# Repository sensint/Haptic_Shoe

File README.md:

<div id="top"></div>

<!-- PROJECT SHIELDS -->
<!--
*** I'm using markdown "reference style" links for readability.
*** Reference links are enclosed in brackets [ ] instead of parentheses ( ).
*** See the bottom of this document for the declaration of the reference variables
*** for contributors-url, forks-url, etc. This is an optional, concise syntax you may use.
*** https://www.markdownguide.org/basic-syntax/#reference-style-links
-->
[![Contributors][contributors-shield]][contributors-url]
[![Forks][forks-shield]][forks-url]
[![Stargazers][stars-shield]][stars-url]
[![Issues][issues-shield]][issues-url]
[![MIT License][license-shield]][license-url]

<!-- PROJECT LOGO -->
<br />
<div align="center">

<h3 align="center">Haptic Shoe</h3>

  <p align="center">
    An Open Source Experimental Haptic Shoe for Augmented Tactile Reality
    <br />
    <br />
    <a href="https://github.com/sensint/Haptic_Shoe/issues">Report Bug</a>
    ·
    <a href="https://github.com/sensint/Haptic_Shoe/issues">Request Feature</a>
  </p>
</div>

## About The Project

![Banner images][banner-image]

<!--Add a summary of the project.-->

<p align="right">(<a href="#top">back to top</a>)</p>

### Built With

* [Teensy](https://www.pjrc.com/teensy/) and [Teensy Audio Library](https://www.pjrc.com/teensy/td_libs_Audio.html)
* [PlatformIO](https://platformio.org/)
* [Fusion 360](https://www.autodesk.com/products/fusion-360)
* [KiCad EDA](https://www.kicad.org/)

<p align="right">(<a href="#top">back to top</a>)</p>

## Getting Started

Download the code from the GitHub website or clone the repository using your favorite git-client software or with the following command:

   ```sh
   git clone https://github.com/sensint/Haptic_Shoe.git
   ```

### Firmware

<p align="right">(<a href="#top">back to top</a>)</p>

### Hardware

<p align="right">(<a href="#top">back to top</a>)</p>

## Usage

<!--Use this space to show useful examples of how a project can be used. Additional screenshots, code examples and demos work well in this space. You may also link to more resources.-->

<p align="right">(<a href="#top">back to top</a>)</p>

## Roadmap

See the [open issues](https://github.com/sensint/Haptic_Shoe/issues) for a full list of proposed features (and known issues).

### Firmware

- [ ] ...

### Hardware

- [ ] ...

<p align="right">(<a href="#top">back to top</a>)</p>

## Contributing

Contributions are what make the open source community such an amazing place to learn, inspire, and create. Any contributions you make are **greatly appreciated**.

If you have a suggestion that would make this better, please fork the repo and create a pull request. You can also simply open an issue with the tag "enhancement".
Don't forget to give the project a star! Thanks again!

1. Fork the Project
2. Create your Feature Branch (`git checkout -b feature/AmazingFeature`)
3. Commit your Changes (`git commit -m 'Add some AmazingFeature'`)
4. Push to the Branch (`git push origin feature/AmazingFeature`)
5. Open a Pull Request

<p align="right">(<a href="#top">back to top</a>)</p>

## License

Distributed under the MIT License. See `LICENSE.txt` for more information.

<p align="right">(<a href="#top">back to top</a>)</p>

## Contact

Sensorimotor Interaction Group - [website](https://sensint.mpi-inf.mpg.de/) - [@sensintgroup](https://twitter.com/sensintgroup)

Project Link: [https://github.com/sensint/Haptic_Shoe](https://github.com/sensint/Haptic_Shoe)

<p align="right">(<a href="#top">back to top</a>)</p>

## Acknowledgments

* Othneil Drew for [Best-README-Template](https://github.com/othneildrew/Best-README-Template)

<p align="right">(<a href="#top">back to top</a>)</p>

<!-- MARKDOWN LINKS & IMAGES -->
<!-- https://www.markdownguide.org/basic-syntax/#reference-style-links -->
[contributors-shield]: https://img.shields.io/github/contributors/sensint/Haptic_Shoe.svg?style=for-the-badge
[contributors-url]: https://github.com/sensint/Haptic_Shoe/graphs/contributors
[forks-shield]: https://img.shields.io/github/forks/sensint/Haptic_Shoe.svg?style=for-the-badge
[forks-url]: https://github.com/sensint/Haptic_Shoe/network/members
[stars-shield]: https://img.shields.io/github/stars/sensint/Haptic_Shoe.svg?style=for-the-badge
[stars-url]: https://github.com/sensint/Haptic_Shoe/stargazers
[issues-shield]: https://img.shields.io/github/issues/sensint/Haptic_Shoe.svg?style=for-the-badge
[issues-url]: https://github.com/sensint/Haptic_Shoe/issues
[license-shield]: https://img.shields.io/github/license/sensint/Haptic_Shoe.svg?style=for-the-badge
[license-url]: https://github.com/sensint/Haptic_Shoe/blob/master/LICENSE
[banner-image]: assets/img/banner.png

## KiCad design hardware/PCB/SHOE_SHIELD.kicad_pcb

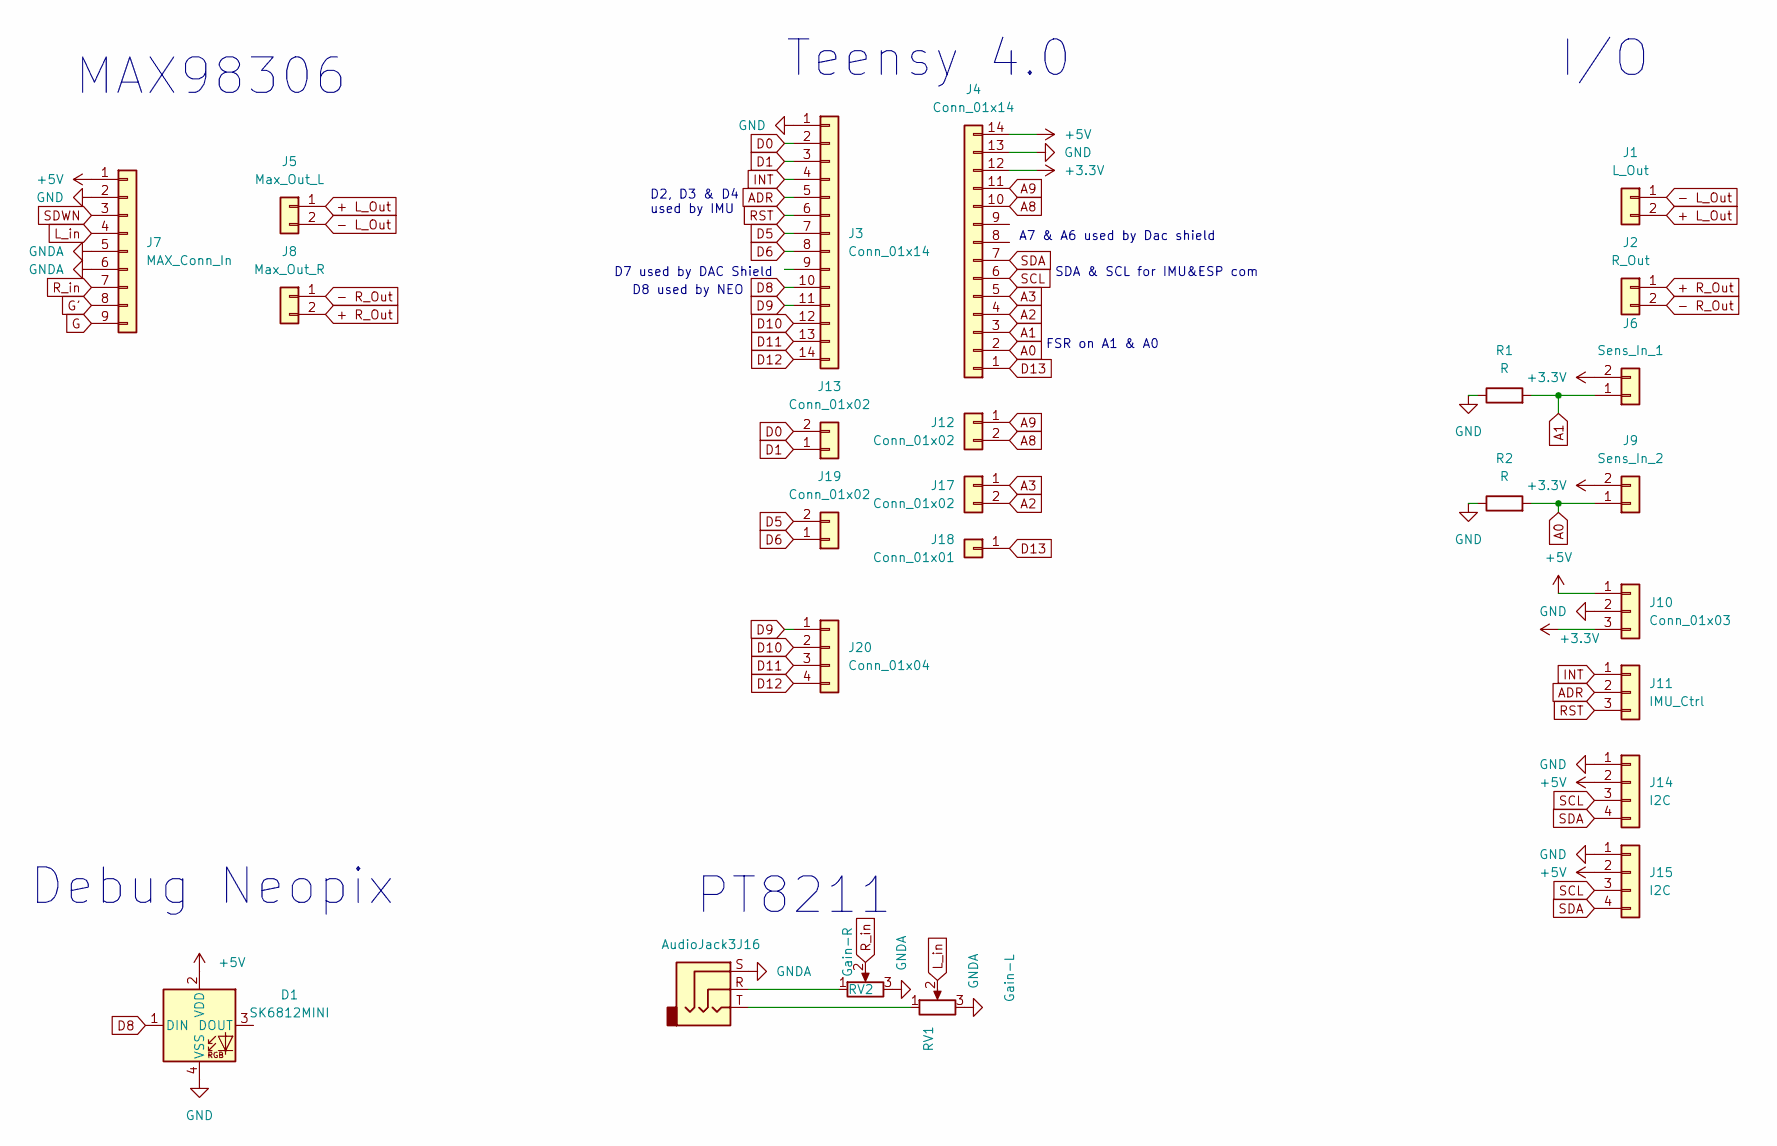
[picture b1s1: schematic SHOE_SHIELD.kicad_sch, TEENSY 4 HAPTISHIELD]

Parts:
D1: SK6812MINI; LED_SK6812MINI_PLCC4_3.5x3.5mm_P1.75mm
J1: L_Out; PinHeader_1x02_P2.54mm_Vertical
J2: R_Out; PinHeader_1x02_P2.54mm_Vertical
J3, J4: Conn_01x14; PinSocket_1x14_P2.54mm_Vertical
J5: Max_Out_L; TerminalBlock_MetzConnect_Type059_RT06302HBWC_1x02_P3.50mm_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
J6: Sens_In_1; PinHeader_1x02_P2.54mm_Vertical
J7: MAX_Conn_In; PinSocket_1x09_P2.54mm_Vertical
J8: Max_Out_R; TerminalBlock_MetzConnect_Type059_RT06302HBWC_1x02_P3.50mm_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
J9: Sens_In_2; PinHeader_1x02_P2.54mm_Vertical
J10: Conn_01x03; PinHeader_1x03_P2.54mm_Vertical
J11: IMU_Ctrl; PinHeader_1x03_P2.54mm_Vertical
J12, J13, J17, J19: Conn_01x02; PinHeader_1x02_P2.54mm_Vertical
J14, J15: I2C; PinHeader_1x04_P2.54mm_Vertical
J16: AudioJack3; Jack_3.5mm_CUI_SJ1-3525N_Horizontal
J18: Conn_01x01; PinHeader_1x01_P2.54mm_Vertical
J20: Conn_01x04; PinHeader_1x04_P2.54mm_Vertical
R1, R2: R; R_Axial_DIN0204_L3.6mm_D1.6mm_P2.54mm_Vertical
RV1: Gain-L; Potentiometer_Runtron_RM-065_Vertical
RV2: Gain-R; Potentiometer_Runtron_RM-065_Vertical

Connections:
+3V3: J4.12, J6.2, J9.2, J10.3
+5V: D1.2 (VDD), J4.14, J7.1, J10.1, J14.2, J15.2
+ L_Out: J1.2, J5.1
+ R_Out: J2.1, J8.2
- L_Out: J1.1, J5.2
- R_Out: J2.2, J8.1
A0: J4.2, J9.1, R2.2
A1: J4.3, J6.1, R1.2
A2: J4.4, J17.2
A3: J4.5, J17.1
A8: J4.10, J12.2
A9: J4.11, J12.1
ADR: J3.5, J11.2
D0: J3.2, J13.2
D1: J3.3, J13.1
D5: J3.7, J19.2
D6: J3.8, J19.1
D8: D1.1 (DIN), J3.10
D9: J3.11, J20.1
D10: J3.12, J20.2
D11: J3.13, J20.3
D12: J3.14, J20.4
D13: J4.1, J18.1
G: J7.9
G': J7.8
GND: D1.4 (VSS), J3.1, J4.13, J7.2, J10.2, J14.1, J15.1, R1.1, R2.1
GNDA: J7.5, J7.6, J16.S, RV1.3, RV2.3
INT: J3.4, J11.1
L_in: J7.4, RV1.2
unnamed: J16.R, RV2.1
unnamed: J16.T, RV1.1
RST: J3.6, J11.3
R_in: J7.7, RV2.2
SCL: J4.6, J14.3, J15.3
SDA: J4.7, J14.4, J15.4
SDWN: J7.3

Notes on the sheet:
PT8211
D2, D3 & D4 used by IMU
SDA & SCL for IMU&ESP com
Teensy 4.0
FSR on A1 & A0
D7 used by DAC Shield
A7 & A6 used by Dac shield
D8 used by NEO
I/O
Debug Neopix
MAX98306

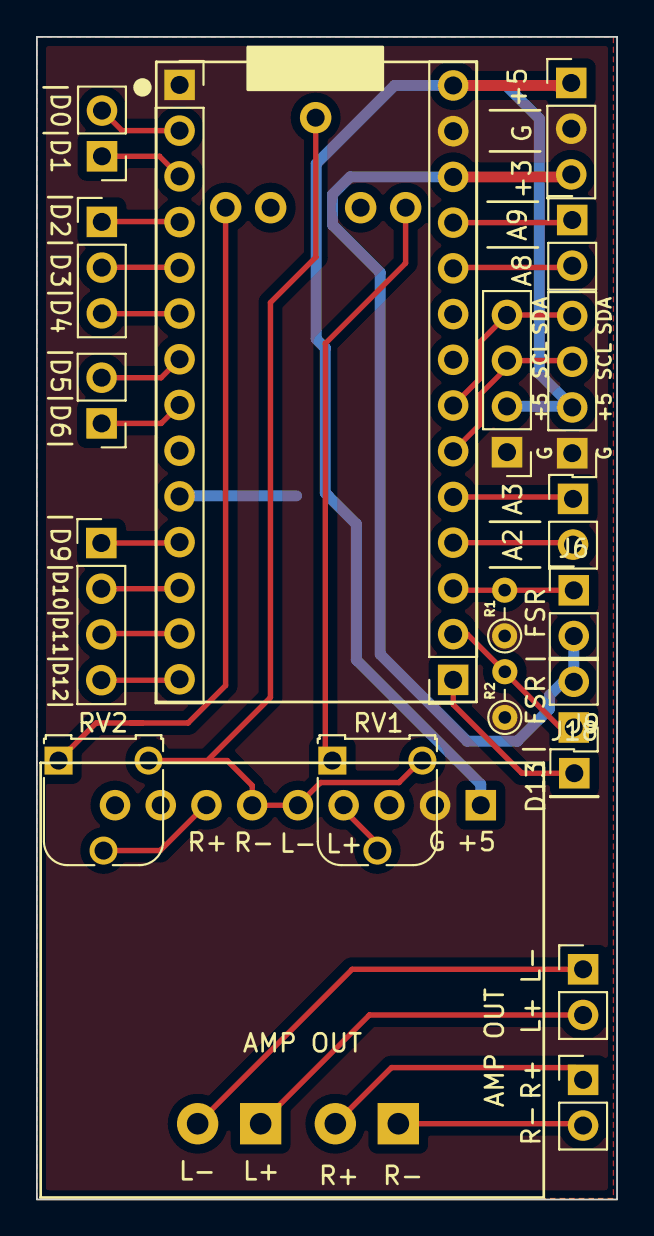
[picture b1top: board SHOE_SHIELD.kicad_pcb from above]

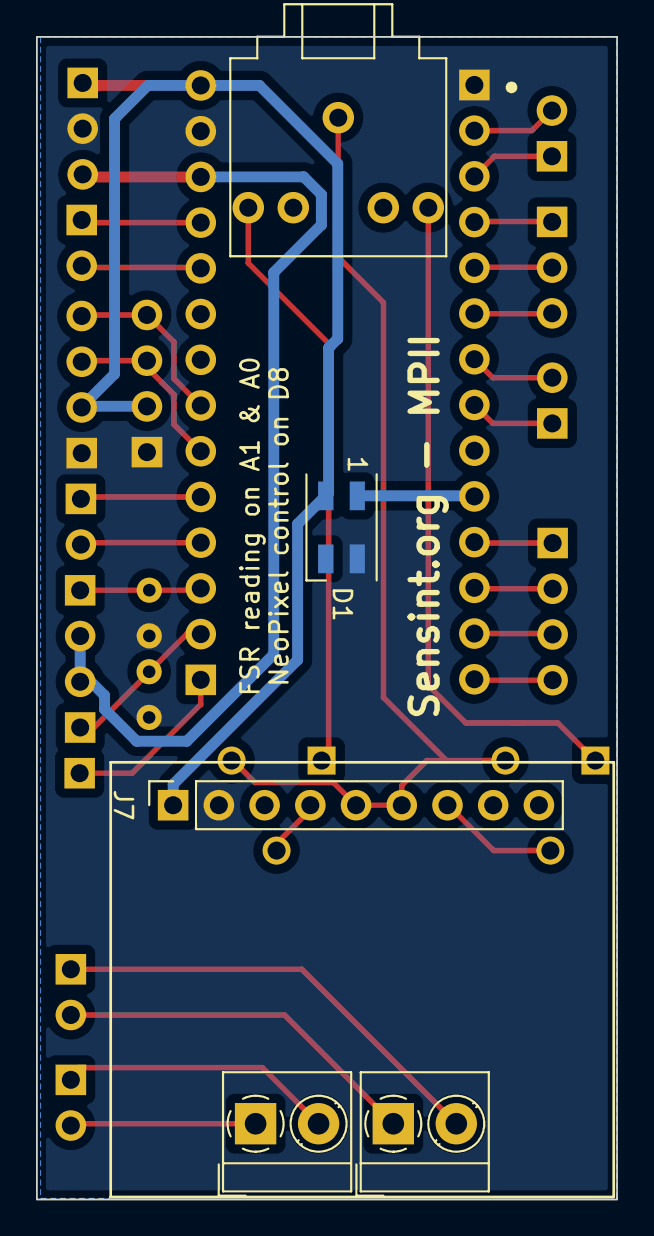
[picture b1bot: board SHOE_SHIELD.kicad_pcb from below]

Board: 2 copper layers, 32.2 x 64.6 mm, 25 parts (5 on the bottom side), 33 nets.

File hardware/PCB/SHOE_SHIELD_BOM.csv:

"Id";"Designator";"Package";"Quantity";"Designation";"Supplier and ref";
1;"R1,R2";"R_Axial_DIN0204_L3.6mm_D1.6mm_P2.54mm_Vertical";2;"R";;;
2;"J1";"PinHeader_1x02_P2.54mm_Vertical";1;"L_Out";;;
3;"J13,J12,J19,J17";"PinHeader_1x02_P2.54mm_Vertical";4;"Conn_01x02";;;
4;"J14,J15";"PinHeader_1x04_P2.54mm_Vertical";2;"I2C";;;
5;"J10";"PinHeader_1x03_P2.54mm_Vertical";1;"Conn_01x03";;;
6;"J6";"PinHeader_1x02_P2.54mm_Vertical";1;"Sens_In_1";;;
7;"J9";"PinHeader_1x02_P2.54mm_Vertical";1;"Sens_In_2";;;
8;"J11";"PinHeader_1x03_P2.54mm_Vertical";1;"IMU_Ctrl";;;
9;"RV1";"Potentiometer_Runtron_RM-065_Vertical";1;"Gain-L";;;
10;"J20";"PinHeader_1x04_P2.54mm_Vertical";1;"Conn_01x04";;;
11;"J2";"PinHeader_1x02_P2.54mm_Vertical";1;"R_Out";;;
12;"J4,J3";"PinSocket_1x14_P2.54mm_Vertical";2;"Conn_01x14";;;
13;"RV2";"Potentiometer_Runtron_RM-065_Vertical";1;"Gain-R";;;
14;"J18";"PinHeader_1x01_P2.54mm_Vertical";1;"Conn_01x01";;;
15;"D1";"LED_SK6812MINI_PLCC4_3.5x3.5mm_P1.75mm";1;"SK6812MINI";;;
16;"J16";"Jack_3.5mm_CUI_SJ1-3525N_Horizontal";1;"AudioJack3";;;
17;"J7";"PinSocket_1x09_P2.54mm_Vertical";1;"MAX_Conn_In";;;
18;"J5";"TerminalBlock_MetzConnect_Type059_RT06302HBWC_1x02_P3.50mm_Horizontal";1;"Max_Out_L";;;
19;"J8";"TerminalBlock_MetzConnect_Type059_RT06302HBWC_1x02_P3.50mm_Horizontal";1;"Max_Out_R";;;
